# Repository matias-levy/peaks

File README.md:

# $peaks, a fully-functional low-cost reversion of [Mutable instrument's Peaks](https://mutable-instruments.net/modules/peaks/)

## Motivation
Where I am from it is sometimes very difficult to source components for digital Eurorack modules, but I had my eyes on Peaks for a long time and I wanted to do something cheap with the same functionality. The basic premise was to use a bluepill (stm32f103c8t6 development board) and omit the DAC IC, relying on a technic called dual PWM as it is described in [openmusiclabs blog](http://www.openmusiclabs.com/learning/digital/pwm-dac/dual-pwm-circuits/index.html) and used, for example, in the popular [Mozzi Library](https://github.com/sensorium/Mozzi) for Arduino.

## Description
The project uses a single sided home-etched PCB with a couple of jumper wires, the potentiometers are regular 16mm ones mounted at the side, also helping with the mechanical stability of the build. <br>
You will need a bluepill capable of 128kb of flash, I bought mine advertised as only having 64kb, but it ended up not being the case, so it's worth the try

## Firmwares
There's the option to flash one of two firmwares that where ported. The original Mutable Instruments one is in the firmware/peaks directory. The [Mutated Mutables Dead Man's Catch](https://github.com/timchurches/Mutated-Mutables/tree/master/peaks) is in the firmware/peaks2. The later adds a lot of functionality to the module, although the UI becomes a bit confusing. <br>
Compiled binaries and HEX files are provided for both under firmware/build.

## Changes
* Added a driver for the PWM DAC running at **14 bit depth, 48Khz sampling rate.** (File in firmware/peaks/drivers/pwm_dac.h)
* Activated the clock for the TIM4 in firmware/peaks/drivers/system.cc
* **Bypassed the bootloader:** This was done as to simplify the code, it does not interfere with the calibration functionality of the module.
* Redesigned the output portion of the hardware to accommodate to the PWM levels. 

## Flashing and development
To make it easier I have left binaries and .HEX files in firmware/build, this can be flashed directly to the bluepill using [STM32CubeProgrammer](https://www.st.com/en/development-tools/stm32cubeprog.html). <br>
Another option is to install the [mutable-dev-environment](https://github.com/pichenettes/mutable-dev-environment) and replace the peaks folder with the one inside /firmware, then executing

    make -f peaks/makefile upload_serial

We use this command because the bootloader is bypassed.

## Thanks
I want to thank Emilie Gillet for open-sourcing her work which is a constant inspiration for many musicians and makers, and encourage everyone interested in this project to checkout the [Mutable instrument's Forum](https://forum.mutable-instruments.net/) in which Emilie is a very active member.

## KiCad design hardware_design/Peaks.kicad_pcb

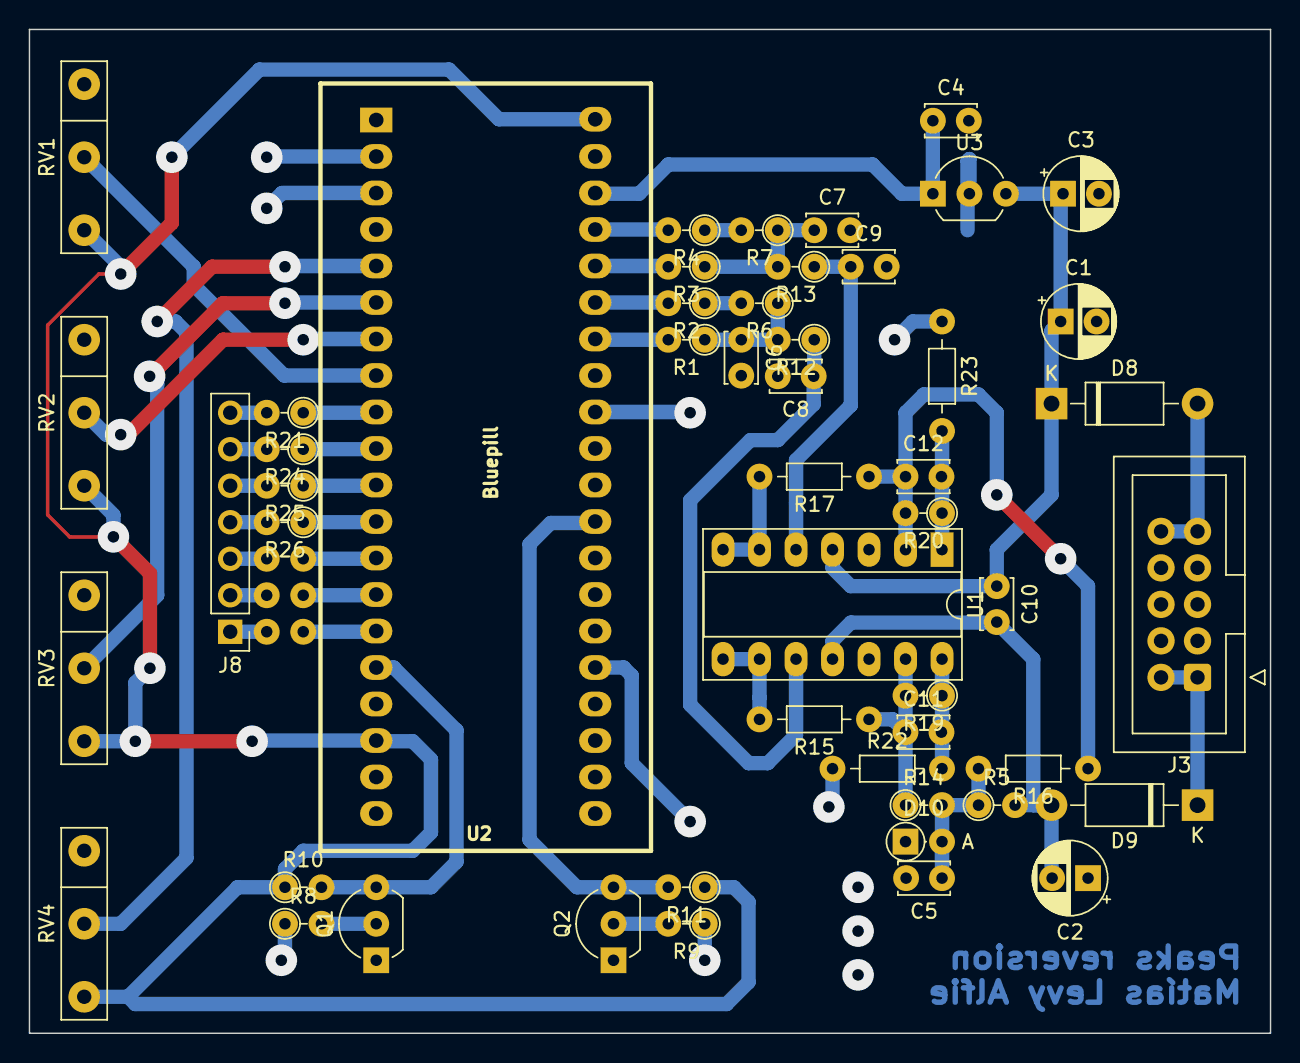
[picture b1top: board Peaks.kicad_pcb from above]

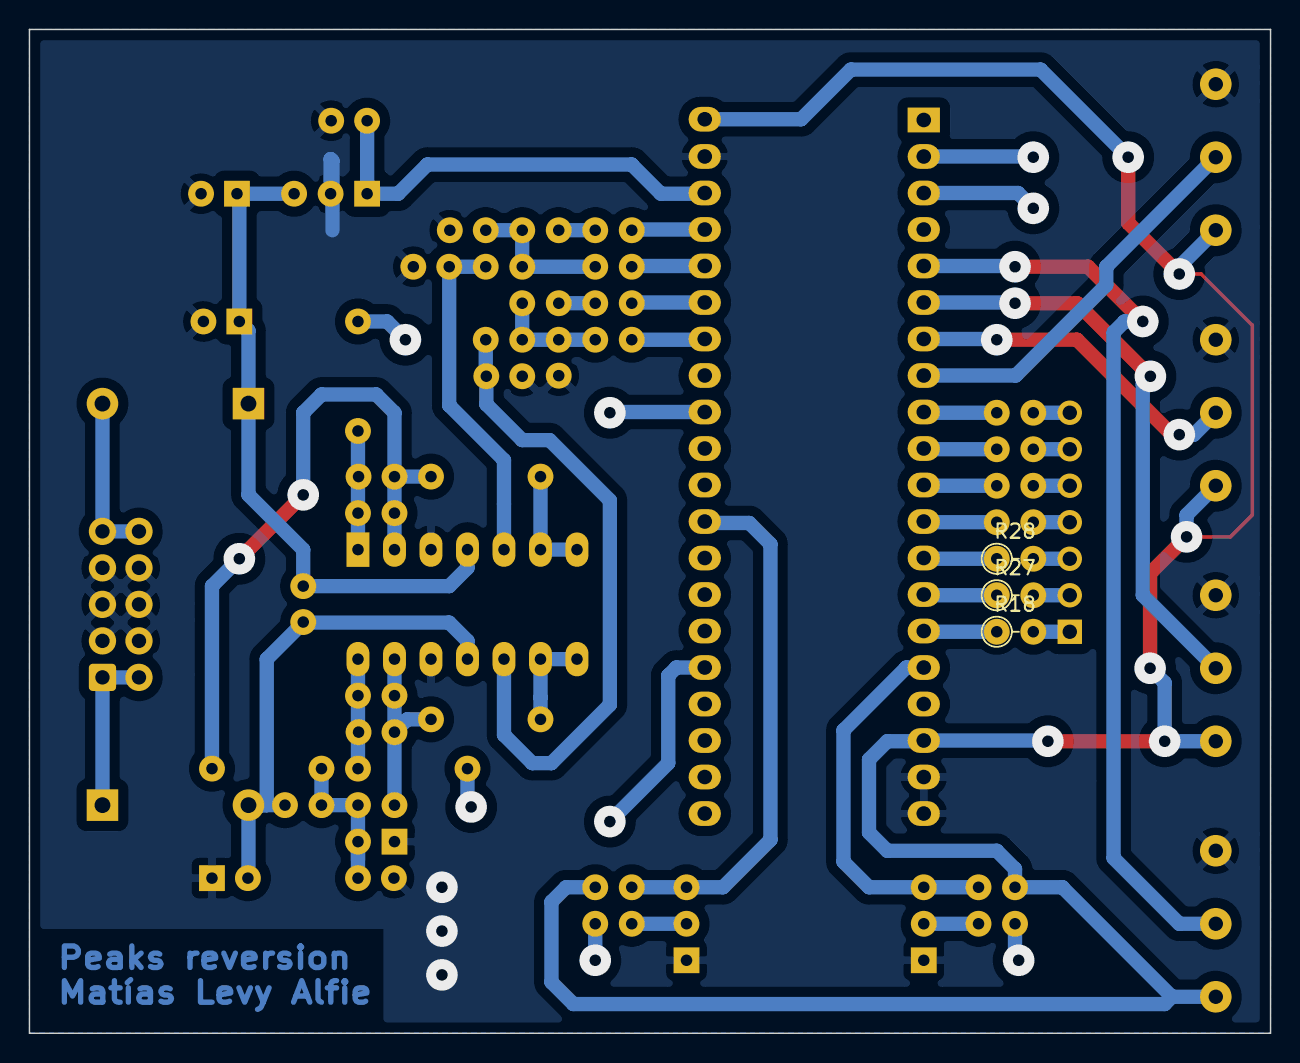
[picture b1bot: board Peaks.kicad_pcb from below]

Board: 2 copper layers, 86.4 x 69.8 mm, 54 parts (3 on the bottom side), 46 nets.

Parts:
C1, C2: 10u; CP_Radial_D5.0mm_P2.50mm_Large_Pads
C3: 0,33u; CP_Radial_D5.0mm_P2.50mm_Large_Pads
C4, C5, C10: 100n; C_Disc_D3.4mm_W2.1mm_P2.50mm_Large_Pads
C6, C7, C8, C9: 4.7n; C_Disc_D3.4mm_W2.1mm_P2.50mm_Large_Pads
C11, C12: 150pf; C_Disc_D3.4mm_W2.1mm_P2.50mm_Large_Pads
D8, D9: 1N5817; D_DO-41_SOD81_P10.16mm_Horizontal
D10: 3.6; D_DO-35_SOD27_P2.54mm_Vertical_AnodeUp_Large_Pads
J3: Eurorack Power; IDC-Header_2x05_P2.54mm_Vertical_Large_Pads
J8: Conn_01x07; PinHeader_1x07_P2.54mm_Vertical
Q1, Q2: 2N3904; TO-92_Inline_Wide_Large_Pads
R1, R3, R12, R13: 1k5; R_Axial_DIN0204_L3.6mm_D1.6mm_P2.54mm_Vertical_Large_Pads
R2, R4: 180k; R_Axial_DIN0204_L3.6mm_D1.6mm_P2.54mm_Vertical_Large_Pads
R5, R10, R11: 10k; R_Axial_DIN0204_L3.6mm_D1.6mm_P2.54mm_Vertical_Large_Pads
R6, R7: 12k; R_Axial_DIN0204_L3.6mm_D1.6mm_P2.54mm_Vertical_Large_Pads
R8, R9: 100k; R_Axial_DIN0204_L3.6mm_D1.6mm_P2.54mm_Vertical_Large_Pads
R14: 15k; R_Axial_DIN0204_L3.6mm_D1.6mm_P2.54mm_Vertical_Large_Pads
R15, R17: 6k8; R_Axial_DIN0204_L3.6mm_D1.6mm_P7.62mm_Horizontal_Large_Pads
R16: 15k; R_Axial_DIN0204_L3.6mm_D1.6mm_P7.62mm_Horizontal_Large_Pads
R18, R21, R24, R25, R26, R27, R28: 2k; R_Axial_DIN0204_L3.6mm_D1.6mm_P2.54mm_Vertical_Large_Pads
R19, R20: 33k; R_Axial_DIN0204_L3.6mm_D1.6mm_P2.54mm_Vertical_Large_Pads
R22, R23: 1k; R_Axial_DIN0204_L3.6mm_D1.6mm_P7.62mm_Horizontal_Large_Pads
RV1, RV2, RV3, RV4: B10k; Potenciometro
U1: TL074; DIP-14_W7.62mm_Socket_LongPads
U2: Bluepill; BluePill_STM32F103C
U3: 78l05; TO-92_Inline_Wide_Large_Pads

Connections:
+3V3: R10.1, R11.1, RV1.3, RV2.3, RV3.3, RV4.3, U2.18, U2.40
+5V: C4.1, U2.38, U3.1
+12V: C1.1, C3.1, C10.1, D8.1, U1.4, U3.3
-12V: C2.2, C10.2, D9.2, R5.2, U1.11
/CH1_PWM1: R1.2, U2.34
/CH1_PWM2: R2.2, U2.35
/CH2_PWM1: R3.2, U2.36
/CH2_PWM2: R4.2, U2.37
/LED1: R18.1, U2.15
/LED2: R21.1, U2.9
/LED3: R24.1, U2.10
/LED4: R25.1, U2.11
/LED5: R26.1, U2.12
/LED_SALIDA_1: R27.1, U2.14
/LED_SALIDA_2: R28.1, U2.13
/POT_1: RV1.2, U2.8
/POT_2: RV2.2, U2.7
/POT_3: RV3.2, U2.6
/POT_4: RV4.2, U2.5
/REF_-3.6: C5.1, D10.2, R5.1, R14.2, R16.2
/TRIG_1: Q1.3, R10.2, U2.16
/TRIG_2: Q2.3, R11.2, U2.29
GND: C1.2, C2.1, C3.2, C4.2, C5.2, C6.2, C7.2, C8.2, C9.2, D10.1, J3.3, J3.4, J3.5, J3.6, J3.7, J3.8, Q1.1, Q2.1, RV1.1, RV2.1, RV3.1, RV4.1, U1.3, U1.12, U2.19, U2.20, U2.39, U3.2
unnamed: C6.1, R1.1, R6.1, R12.2
unnamed: C7.1, R3.1, R7.1, R13.2
unnamed: C8.1, R12.1, U1.10
unnamed: C9.1, R13.1, U1.5
unnamed: C11.1, R14.1, R15.1, R19.2, U1.13
unnamed: C11.2, R19.1, R22.2, U1.14
unnamed: C12.1, R16.1, R17.1, R20.2, U1.2
unnamed: C12.2, R20.1, R23.2, U1.1
unnamed: D8.2, J3.9, J3.10
unnamed: D9.1, J3.1, J3.2
unnamed: Q1.2, R8.2
unnamed: Q2.2, R9.2
unnamed: R2.1, R6.2
unnamed: R4.1, R7.2
unnamed: R15.2, U1.8, U1.9
unnamed: R17.2, U1.6, U1.7
TO_D1: J8.1, R18.2
TO_D2: J8.7, R21.2
TO_D3: J8.6, R24.2
TO_D4: J8.5, R25.2
TO_D5: J8.4, R26.2
TO_D6: J8.2, R27.2
TO_D7: J8.3, R28.2

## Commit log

2021-02-14 Ported Dead Man's Catch Alternative firmware
2021-02-14 Added Personal footprint library in hardware_design
2021-02-14 Added Schematic.pdf
2021-02-17 Spelling on README
